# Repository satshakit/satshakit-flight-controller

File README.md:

<h1 style="font-family: courier;" align="center"> satshakit flight controller</h1>
<p align="center">

<div align="center"><i>An open source & easy to make flight controller board.</i></div>
</p>  

satshakit flight controller
--
satshakit flight controller is an **open source, MultiWii compatible, flight controller board**, that is possibile to **make in a FabLab**. The design derives from both a **satshakit board** and dual processor flight controller of my **[FabAcademy2015 final project](http://fabacademy.org/archives/2015/eu/students/ingrassia.daniele/index.html)**.

Here you can find all of the satshakit boards: **[satshakit organization](https://github.com/satshakit)**.

Features
--

satshakit flight controller has been designed aiming to be **easy to make, program and use**, so to be possible to **replicate and customize it** in any other Fab Lab. It has the following features:

- support for [any drone configuration](http://www.multiwii.com/connecting-elements) up to **8 motors**
- support for up to **6 channels** receivers 
- costs about **8€**
- **16mhz crystal** for precise clock, reliability and compatibility
- size of **48x48mmm** to fit the size of commercial available boards
- embedded **power board** (if needed)
- possibility to connect and use **any IMU working at 5V**

You can use satshakit flight controller in **DIY drones** or, due the dimensions are the same or less of most of the MultiWii commercial flight controller boards (50x50mmm), as a **replacement flight controller for commercial drones**. For drones up to 4 motors and 15A ESCs, is possible to use the **embedded power board**, otherwise is recommended to use an external power board, and to make the satshakit flight controller without the power board embedded.

Getting started
--

After you finish to solder a satshakit flight controller board, you need to **set its fuses and to program it with MultiWii**. To set the fuses you can easily upload the Arduino Bootloader using Arduino IDE and an **Arduino as ISP**. To do so first upload the Arduino as ISP sketch into an Arduino, and then connect the satshakit flight controller as following (this is the same for the version with the power board and without):

Once everything is connected, follow these steps to upload Arduino bootloader:

1. open Arduino IDE
2. select proper programmer (for example Arduino as ISP or USBtinyISP)
3. select Arduino UNO as board
4. click on tools->Burn Bootloader

Now you can use again the same connections, Arduino as ISP and Arduino IDE  to **upload your favourite MultiWii** version, this time using **File->Upload using a programmer**.

To connect all the elements fo your drone, you can follow the **satshakit flight controller pinout**:

satshakit flight controller pinout with **embedded power power board:**

Downloads
--

**downloads (right click, download as)**

- [satshakit flight controller sch](https://raw.githubusercontent.com/satshakit/satshakit-flight-controller/master/eagle_projects/satshakit_flight_controller/satshakit_fc.sch)
- [satshakit flight controller brd](https://raw.githubusercontent.com/satshakit/satshakit-flight-controller/master/eagle_projects/satshakit_flight_controller/satshakit_fc.brd)
- [satshakit flight controller svg](https://raw.githubusercontent.com/satshakit/satshakit-flight-controller/master/media/satshakit_flight_controller/satshakit_fc.svg)
- [satshakit flight controller internal](https://raw.githubusercontent.com/satshakit/satshakit-flight-controller/master/media/satshakit_flight_controller/satshakit_fc_internal.png)
- [satshakit flight controller holes](https://raw.githubusercontent.com/satshakit/satshakit-flight-controller/master/media/satshakit_flight_controller/satshakit_fc_holes.png)
- [satshakit flight controller cut](https://raw.githubusercontent.com/satshakit/satshakit-flight-controller/master/media/satshakit_flight_controller/satshakit_fc_cut.png)
- [satshakit flight controller cut tip](https://raw.githubusercontent.com/satshakit/satshakit-flight-controller/master/media/satshakit_flight_controller/satshakit_fc_cut_tip.png)
- [satshakit flight controller with power board sch](https://raw.githubusercontent.com/satshakit/satshakit-flight-controller/master/eagle_projects/satshakit_flight_controller_power/satshakit_fc_power.sch)
- [satshakit flight controller with power board brd](https://raw.githubusercontent.com/satshakit/satshakit-flight-controller/master/eagle_projects/satshakit_flight_controller_power/satshakit_fc_power.brd)
- [satshakit flight controller with power board svg](https://raw.githubusercontent.com/satshakit/satshakit-flight-controller/master/media/satshakit_flight_controller_power/satshakit_fc_power.svg)
- [satshakit flight controller with power board internal](https://raw.githubusercontent.com/satshakit/satshakit-flight-controller/master/media/satshakit_flight_controller_power/satshakit_fc_power_internal.png)
- [satshakit flight controller with power board holes](https://raw.githubusercontent.com/satshakit/satshakit-flight-controller/master/media/satshakit_flight_controller_power/satshakit_fc_power_holes.png)
- [satshakit flight controller with power board cut](https://raw.githubusercontent.com/satshakit/satshakit-flight-controller/master/media/satshakit_flight_controller_power/satshakit_fc_power_cut.png)
- [satshakit flight controller with power board cut tip](https://raw.githubusercontent.com/satshakit/satshakit-flight-controller/master/media/satshakit_flight_controller_power/satshakit_fc_power_cut_tip.png)
- [satshakit flight controller BOM xlsx](https://raw.githubusercontent.com/satshakit/satshakit-flight-controller/master/docs/satshakit_fc_BOM.xlsx)
- [satshakit flight controller BOM ods](https://raw.githubusercontent.com/satshakit/satshakit-flight-controller/master/docs/satshakit_fc_BOM.ods)

Media
--

board, soldered and installed satshakit flight controller:

uploading Arduino bootloader:

uploading Multiwii:

Multiwii test:

What's in the repo
--

- **[docs](https://github.com/satshakit/satshakit-flight-controller/tree/master/docs)**: BOM files for Farnell
- **[egle projects](https://github.com/satshakit/satshakit-flight-controller/tree/master/eagle_projects)**: eagle projects of the satshakit flight controller
- **[media](https://github.com/satshakit/satshakit-flight-controller/tree/master/media)**: svgs, connections schemas, images for cnc milling machine, other images

Authors
--

- Daniele Ingrassia

Contact
--

- **ingrassiada@gmail.com**
- **[linkedin](http://it.linkedin.com/in/danieleingrassia)**

Thanks
--

[Fablab Kamp-Lintfort](http://fablab.hochschule-rhein-waal.de/index.php/de/)<br />
Hochschule Rhein-Waal<br />
Friedrich-Heinrich-Allee 25, 47475 Kamp-Lintfort, Germany<br />
fablab@hochschule-rhein-waal.de

License
--
This work is licensed under the terms of the open source license: Creative Commons Attribution-ShareAlike 4.0 International ([CC BY-SA 4.0](https://creativecommons.org/licenses/by-sa/4.0/)).

Disclaimer  
--

<div class="align-justify">
This hardware/software is provided "as is", and you use the hardware/software at your own risk. Under no circumstances shall any author be liable for direct, indirect, special, incidental, or consequential damages resulting from the use, misuse, or inability to use this hardware/software, even if the authors have been advised of the possibility of such damages.</div>

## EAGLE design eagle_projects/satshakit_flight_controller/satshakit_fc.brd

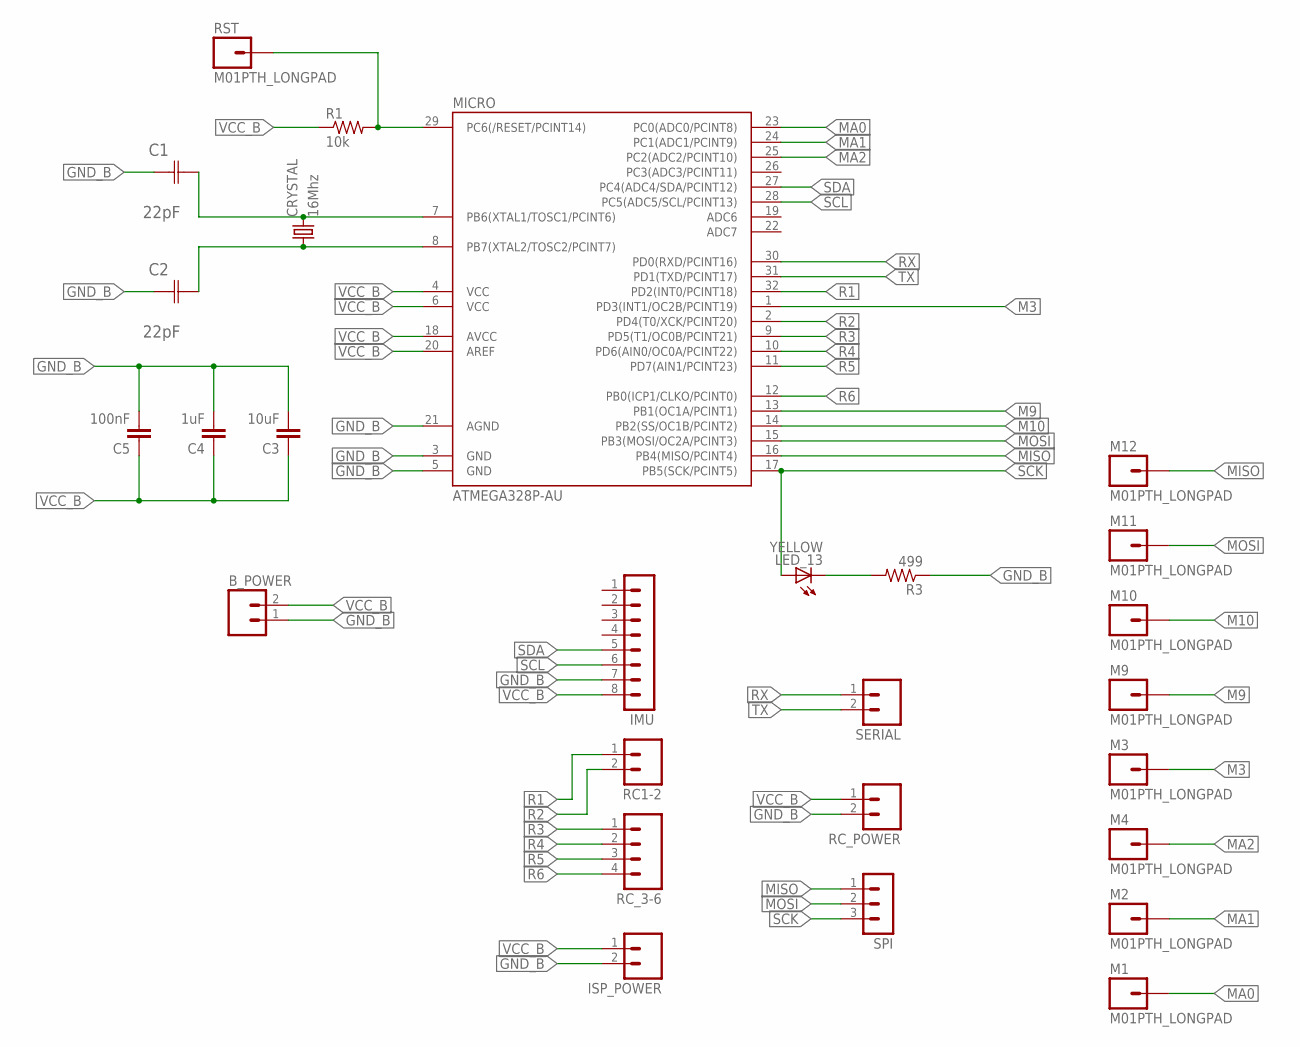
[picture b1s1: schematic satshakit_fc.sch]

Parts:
B_POWER: M02LOCK_LONGPADS; 1X02_LOCK_LONGPADS
C1, C2: 22pF; CAPC3216X178N
C3: 10uF; 1206
C4: 1uF; 1206
C5: 100nF; 1206
CRYSTAL: 16Mhz; CSM-7X-DU
IMU: MA08-1
ISP_POWER: M02LOCK_LONGPADS; 1X02_LOCK_LONGPADS
LED_13: YELLOW; 1206
M1, M2, M3, M4, M9, M10, M11, M12: M01PTH_LONGPAD; 1X01_LONGPAD
MICRO: ATMEGA328P-AU; TQFP32-08
R1: 10k; 1206
R3: 499; 1206
RC1-2: M02; 02P
RC_3-6: M04LONGPADS; 1X04_LONGPADS
RC_POWER: M02LOCK_LONGPADS; 1X02_LOCK_LONGPADS
RST: M01PTH_LONGPAD; 1X01_LONGPAD
SERIAL: M02LOCK_LONGPADS; 1X02_LOCK_LONGPADS
SPI: MA03-1

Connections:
GND_B: B_POWER.1, C1.1 (C1), C2.1 (C1), C3.2, C4.2, C5.2, IMU.7, ISP_POWER.2, MICRO.3 (GND), MICRO.5 (GND), MICRO.21 (AGND), R3.1, RC_POWER.2
M3: M3.1, MICRO.1 (PD3(INT1/OC2B/PCINT19))
M9: M9.1, MICRO.13 (PB1(OC1A/PCINT1))
M10: M10.1, MICRO.14 (PB2(SS/OC1B/PCINT2))
MA0: M1.1, MICRO.23 (PC0(ADC0/PCINT8))
MA1: M2.1, MICRO.24 (PC1(ADC1/PCINT9))
MA2: M4.1, MICRO.25 (PC2(ADC2/PCINT10))
MISO: M12.1, MICRO.16 (PB4(MISO/PCINT4)), SPI.1
MOSI: M11.1, MICRO.15 (PB3(MOSI/OC2A/PCINT3)), SPI.2
unnamed: C1.2 (C2), CRYSTAL.2, MICRO.7 (PB6(XTAL1/TOSC1/PCINT6))
unnamed: MICRO.29 (PC6(/RESET/PCINT14)), R1.2, RST.1
unnamed: C2.2 (C2), CRYSTAL.1, MICRO.8 (PB7(XTAL2/TOSC2/PCINT7))
unnamed: LED_13.2 (C), R3.2
R1: MICRO.32 (PD2(INT0/PCINT18)), RC1-2.1
R2: MICRO.2 (PD4(T0/XCK/PCINT20)), RC1-2.2
R3: MICRO.9 (PD5(T1/OC0B/PCINT21)), RC_3-6.1
R4: MICRO.10 (PD6(AIN0/OC0A/PCINT22)), RC_3-6.2
R5: MICRO.11 (PD7(AIN1/PCINT23)), RC_3-6.3
R6: MICRO.12 (PB0(ICP1/CLKO/PCINT0)), RC_3-6.4
RX: MICRO.30 (PD0(RXD/PCINT16)), SERIAL.1
SCK: LED_13.1 (A), MICRO.17 (PB5(SCK/PCINT5)), SPI.3
SCL: IMU.6, MICRO.28 (PC5(ADC5/SCL/PCINT13))
SDA: IMU.5, MICRO.27 (PC4(ADC4/SDA/PCINT12))
TX: MICRO.31 (PD1(TXD/PCINT17)), SERIAL.2
VCC_B: B_POWER.2, C3.1, C4.1, C5.1, IMU.8, ISP_POWER.1, MICRO.4 (VCC), MICRO.6 (VCC), MICRO.18 (AVCC), MICRO.20 (AREF), R1.1, RC_POWER.1

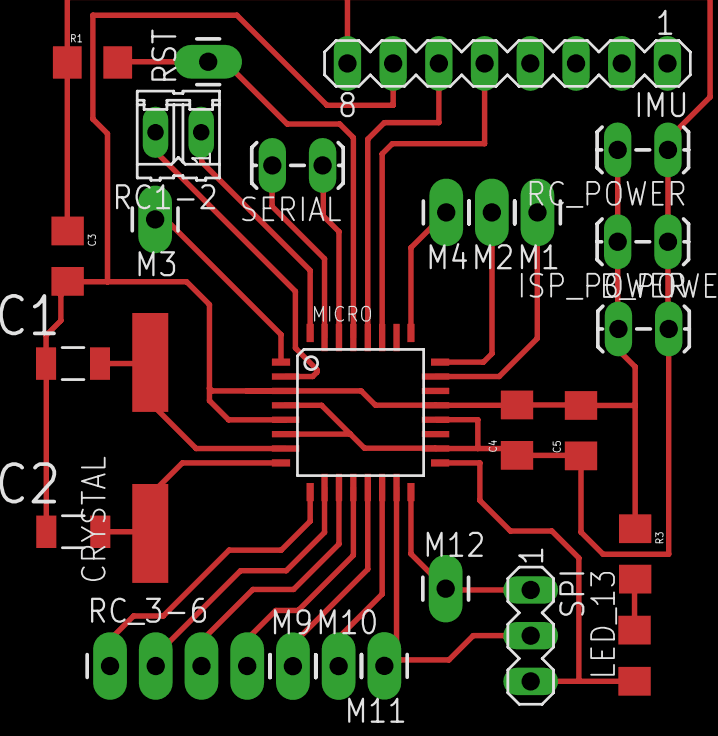
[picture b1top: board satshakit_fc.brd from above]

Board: 2 copper layers, 27 parts (0 on the bottom side), 25 nets.

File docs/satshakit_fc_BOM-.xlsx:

Value | Manufacturer Part No | Package | Description | FARNELL | Price € | Quantity | Min. Quantity Cost €
- | ATMEGA328P-AU | TQFP-32 | microcontroller | 1715486 | 2.78 | 1 | 2.78
16Mhz/18pF | MCRSD16000F183000RR | SMD 11.4 x 4.7 mm | crystal | 2395958 | 0.2 | 1 | 0.2
yellow | MCL-S250YC | 1206 | yellow led | 1581231 | 0.05 | 1 | 0.26
10K | ERJ8GEYJ103V | 1206 | resistor | 2057856 | 0.026 | 1 | 0.26
499 | CRCW1206499RFKEA | 1206 | resistor | 1470020 | 0.028 | 1 | 0.28
22pF | MC1206N220J500CT | 1206 | capacitor | 2320891 | 0.047 | 2 | 0.47
10uF | MC1206X106K250CT | 1206 | capacitor | 2112753 | 0.154 | 1 | 0.154
1uF | MC1206F105Z500CT | 1206 | capacitor | 1759455 | 0.0634 | 1 | 0.634
100nF | MC1206B104K500CT | 1206 | capacitor | 1759361 | 0.0354 | 1 | 0.35
- | 61304011021 | 2.54 mm | pin header | 2356192 | 1.77 | 1 | 1.77
- | M20-9990246 | 2.54 mm | pin header | 1022247 | 0.0653 | 1 | 0.65
 |  |  |  |  |  |  | Total cost
 |  |  |  |  |  |  | 7.808

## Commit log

2016-05-22 first commit of satshakit flight controller
2016-05-22 documentations fixes
2016-05-22 added programming connections
2016-05-22 readme fix
2016-05-22 added license
2016-05-24 adding documentation
2017-01-22 fixed BOM links
2017-01-22 fixed BOM
2017-01-22 removed the satshakit boards list
2017-10-17 change license file formatting
2020-05-31 license change

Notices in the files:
parts and their libraries:
01_SparkFun: Licensing: CC v3.0 Share-Alike You are welcome to use this library for commercial purposes.
